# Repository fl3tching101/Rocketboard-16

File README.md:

# Rocketboard-16
 16 key RGB backlit macro board/numpad with two EC11 rotary encoder switches and a 128x64 OLED display

In addition to running [QMK](https://qmk.fm/) the Rocketboard 16 is compatible with [VIA](https://caniusevia.com/) for quick and easy configuration.

The firmware is open source and integrated with the QMK project, it can be found [here](https://github.com/qmk/qmk_firmware/tree/master/keyboards/rocketboard_16).

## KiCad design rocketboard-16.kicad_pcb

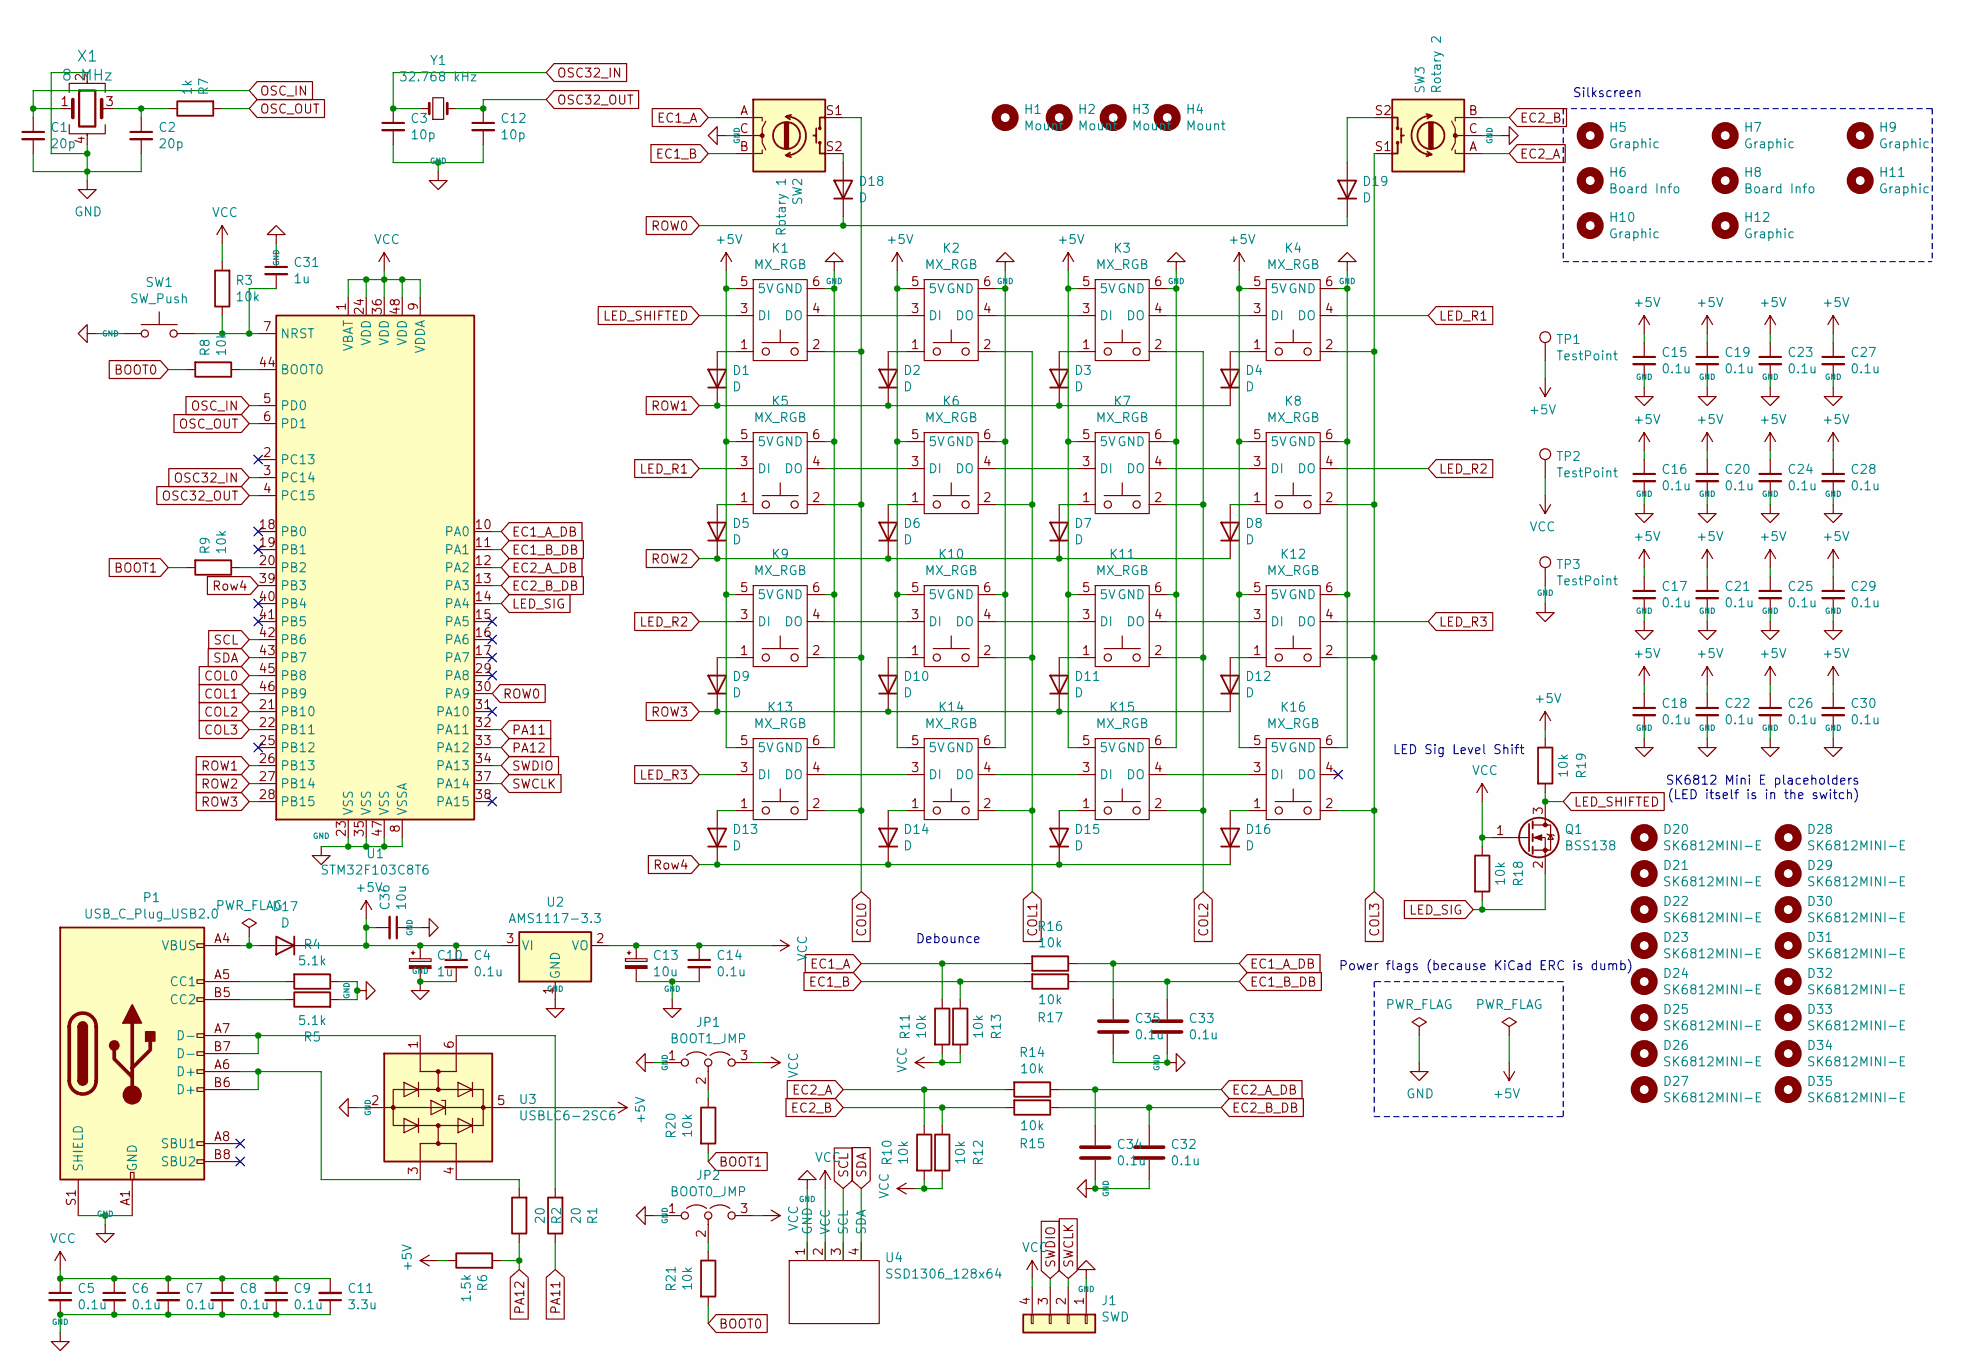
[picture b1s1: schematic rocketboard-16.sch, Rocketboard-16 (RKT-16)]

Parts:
C1, C2: 20p; C_0603_1608Metric
C3, C12: 10p; C_0603_1608Metric
C4, C5, C6, C7, C8, C9, C14, C15, C16, C17, C18, C19, C20, C21, C22, C23, C24, C25, C26, C27, C28, C29, C30, C32, C33, C34, C35: 0.1u; C_0603_1608Metric
C10: 1u; CP_EIA-3216-10_Kemet-I
C11: 3.3u; C_0603_1608Metric
C13: 10u; CP_EIA-3216-10_Kemet-I
C31: 1u; C_0603_1608Metric
C36: 10u; C_0603_1608Metric
D1, D2, D3, D4, D5, D6, D7, D8, D9, D10, D11, D12, D13, D14, D15, D16, D17, D18, D19: D; D_SOD-123
D20, D21, D22, D23, D24, D25, D26, D27, D28, D29, D30, D31, D32, D33, D34, D35: SK6812MINI-E; DUMMY_SK6812MINI-E
H1, H2, H3, H4: Mount; MountingHole_3.2mm_M3
H5: Graphic; saturn_v_simplified
H6: Board Info; board-title
H7: Graphic; lunar_module
H8: Board Info; text
H9: Graphic; space_shuttle
H10: Graphic; iss
H11: Graphic; spacewalk
H12: Graphic; hubble_space_telescope
J1: SWD; PinHeader_1x04_P2.54mm_Vertical
JP1: BOOT1_JMP; SolderJumper-3_P1.3mm_Open_Pad1.0x1.5mm
JP2: BOOT0_JMP; SolderJumper-3_P1.3mm_Open_Pad1.0x1.5mm
K1, K2, K3, K4, K5, K6, K7, K8, K9, K10, K11, K12, K13, K14, K15, K16: MX_RGB; MX_KEYSWITCH_RGB_2D
P1: USB_C_Plug_USB2.0; USB_C_Receptacle_Palconn_UTC16-G
Q1: BSS138; SOT-23
R1, R2: 20; R_0603_1608Metric
R3, R8, R9, R10, R11, R12, R13, R14, R15, R16, R17, R18, R19, R20, R21: 10k; R_0603_1608Metric
R4, R5: 5.1k; R_0603_1608Metric
R6: 1.5k; R_0603_1608Metric
R7: 1k; R_0603_1608Metric
SW1: SW_Push; SW_TS-1187A-B-A-B
SW2: Rotary 1; RotaryEncoder_Alps_EC11E-Switch_Vertical_H20mm_CircularMoun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
SW3: Rotary 2; RotaryEncoder_Alps_EC11E-Switch_Vertical_H20mm_CircularMoun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
TP1, TP2, TP3: TestPoint; TestPoint_Pad_D1.0mm
U1: STM32F103C8T6; LQFP-48_7x7mm_P0.5mm
U2: AMS1117-3.3; SOT-223-3_TabPin2
U3: USBLC6-2SC6; SOT-23-6
U4: SSD1306_128x64; PinHeader_1x04_P2.54mm_Vertical
X1: 8 MHz; Crystal_SMD_5032-4Pin_5.0x3.2mm; Part_num X50328MSB4SI
Y1: 32.768 kHz; Crystal_SMD_3215-2Pin_3.2x1.5mm

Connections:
+5V: C4.1, C10.1, C15.1, C16.1, C17.1, C18.1, C19.1, C20.1, C21.1, C22.1, C23.1, C24.1, C25.1, C26.1, C27.1, C28.1, C29.1, C30.1, C36.2, D17.1 (K), K1.5 (5V), K2.5 (5V), K3.5 (5V), K4.5 (5V), K5.5 (5V), K6.5 (5V), K7.5 (5V), K8.5 (5V), K9.5 (5V), K10.5 (5V), K11.5 (5V), K12.5 (5V), K13.5 (5V), K14.5 (5V), K15.5 (5V), K16.5 (5V), R6.1, R19.1, TP1.1, U2.3 (VI), U3.5 (VBUS)
BOOT0: R8.2, R21.2
BOOT1: R9.2, R20.2
COL0: K1.2, K5.2, K9.2, K13.2, SW2.S1, U1.45 (PB8)
COL1: K2.2, K6.2, K10.2, K14.2, U1.46 (PB9)
COL2: K3.2, K7.2, K11.2, K15.2, U1.21 (PB10)
COL3: K4.2, K8.2, K12.2, K16.2, SW3.S1, U1.22 (PB11)
EC1_A: R11.1, R16.2, SW2.A
EC1_A_DB: C35.1, R16.1, U1.10 (PA0)
EC1_B: R13.1, R17.2, SW2.B
EC1_B_DB: C33.1, R17.1, U1.11 (PA1)
EC2_A: R10.1, R14.2, SW3.A
EC2_A_DB: C34.1, R14.1, U1.12 (PA2)
EC2_B: R12.1, R15.2, SW3.B
EC2_B_DB: C32.1, R15.1, U1.13 (PA3)
GND: C1.2, C2.2, C3.2, C4.2, C5.2, C6.2, C7.2, C8.2, C9.2, C10.2, C11.1, C12.2, C13.2, C14.2, C15.2, C16.2, C17.2, C18.2, C19.2, C20.2, C21.2, C22.2, C23.2, C24.2, C25.2, C26.2, C27.2, C28.2, C29.2, C30.2, C31.1, C32.2, C33.2, C34.2, C35.2, C36.1, J1.1, JP1.1 (A), JP2.1 (A), K1.6 (GND), K2.6 (GND), K3.6 (GND), K4.6 (GND), K5.6 (GND), K6.6 (GND), K7.6 (GND), K8.6 (GND), K9.6 (GND), K10.6 (GND), K11.6 (GND), K12.6 (GND), K13.6 (GND), K14.6 (GND), K15.6 (GND), K16.6 (GND), P1.A1 (GND), P1.A12 (GND), P1.B1 (GND), P1.B12 (GND), P1.S1 (SHIELD), R4.1, R5.2, SW1.1, SW2.C, SW3.C, TP3.1, U1.8 (VSSA), U1.23 (VSS), U1.35 (VSS), U1.47 (VSS), U2.1 (GND), U3.2 (GND), U4.1 (GND), X1.2, X1.4
LED_R1: K4.4 (DO), K5.3 (DI)
LED_R2: K8.4 (DO), K9.3 (DI)
LED_R3: K12.4 (DO), K13.3 (DI)
LED_SHIFTED: K1.3 (DI), Q1.3 (D), R19.2
LED_SIG: Q1.2 (S), R18.2, U1.14 (PA4)
unnamed: C2.1, R7.1, X1.3
unnamed: C31.2, R3.1, SW1.2, U1.7 (NRST)
unnamed: D1.2 (A), K1.1
unnamed: D2.2 (A), K2.1
unnamed: D3.2 (A), K3.1
unnamed: D4.2 (A), K4.1
unnamed: D5.2 (A), K5.1
unnamed: D6.2 (A), K6.1
unnamed: D7.2 (A), K7.1
unnamed: D8.2 (A), K8.1
unnamed: D9.2 (A), K9.1
unnamed: D10.2 (A), K10.1
unnamed: D11.2 (A), K11.1
unnamed: D12.2 (A), K12.1
unnamed: D13.2 (A), K13.1
unnamed: D14.2 (A), K14.1
unnamed: D15.2 (A), K15.1
unnamed: D16.2 (A), K16.1
unnamed: D17.2 (A), P1.A4 (VBUS), P1.A9 (VBUS), P1.B4 (VBUS), P1.B9 (VBUS)
unnamed: D18.2 (A), SW2.S2
unnamed: D19.2 (A), SW3.S2
unnamed: JP1.2 (C), R20.1
unnamed: JP2.2 (C), R21.1
unnamed: K1.4 (DO), K2.3 (DI)
unnamed: K2.4 (DO), K3.3 (DI)
unnamed: K3.4 (DO), K4.3 (DI)
unnamed: K5.4 (DO), K6.3 (DI)
unnamed: K6.4 (DO), K7.3 (DI)
unnamed: K7.4 (DO), K8.3 (DI)
unnamed: K9.4 (DO), K10.3 (DI)
unnamed: K10.4 (DO), K11.3 (DI)
unnamed: K11.4 (DO), K12.3 (DI)
unnamed: K13.4 (DO), K14.3 (DI)
unnamed: K14.4 (DO), K15.3 (DI)
unnamed: K15.4 (DO), K16.3 (DI)
unnamed: P1.A5 (CC1), R4.2
unnamed: P1.A6 (D+), P1.B6 (D+), U3.3 (I/O2)
unnamed: P1.A7 (D-), P1.B7 (D-), U3.1 (I/O1)
unnamed: P1.B5 (CC2), R5.1
unnamed: R1.2, U3.6 (I/O1)
unnamed: R2.2, U3.4 (I/O2)
unnamed: R8.1, U1.44 (BOOT0)
unnamed: R9.1, U1.20 (PB2)
OSC32_IN: C3.1, U1.3 (PC14), Y1.1
OSC32_OUT: C12.1, U1.4 (PC15), Y1.2
OSC_IN: C1.1, U1.5 (PD0), X1.1
OSC_OUT: R7.2, U1.6 (PD1)
PA11: R1.1, U1.32 (PA11)
PA12: R2.1, R6.2, U1.33 (PA12)
ROW0: D18.1 (K), D19.1 (K), U1.30 (PA9)
ROW1: D1.1 (K), D2.1 (K), D3.1 (K), D4.1 (K), U1.26 (PB13)
ROW2: D5.1 (K), D6.1 (K), D7.1 (K), D8.1 (K), U1.27 (PB14)
ROW3: D9.1 (K), D10.1 (K), D11.1 (K), D12.1 (K), U1.28 (PB15)
Row4: D13.1 (K), D14.1 (K), D15.1 (K), D16.1 (K), U1.39 (PB3)
SCL: U1.42 (PB6), U4.3 (SCL)
SDA: U1.43 (PB7), U4.4 (SDA)
SWCLK: J1.2, U1.37 (PA14)
SWDIO: J1.3, U1.34 (PA13)
VCC: C5.1, C6.1, C7.1, C8.1, C9.1, C11.2, C13.1, C14.1, J1.4, JP1.3 (B), JP2.3 (B), Q1.1 (G), R3.2, R10.2, R11.2, R12.2, R13.2, R18.1, TP2.1, U1.1 (VBAT), U1.9 (VDDA), U1.24 (VDD), U1.36 (VDD), U1.48 (VDD), U2.2 (VO), U4.2 (VCC)

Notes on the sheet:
SK6812 Mini E placeholders (LED itself is in the switch)
Power flags (because KiCad ERC is dumb)
Silkscreen
Debounce
LED Sig Level Shift

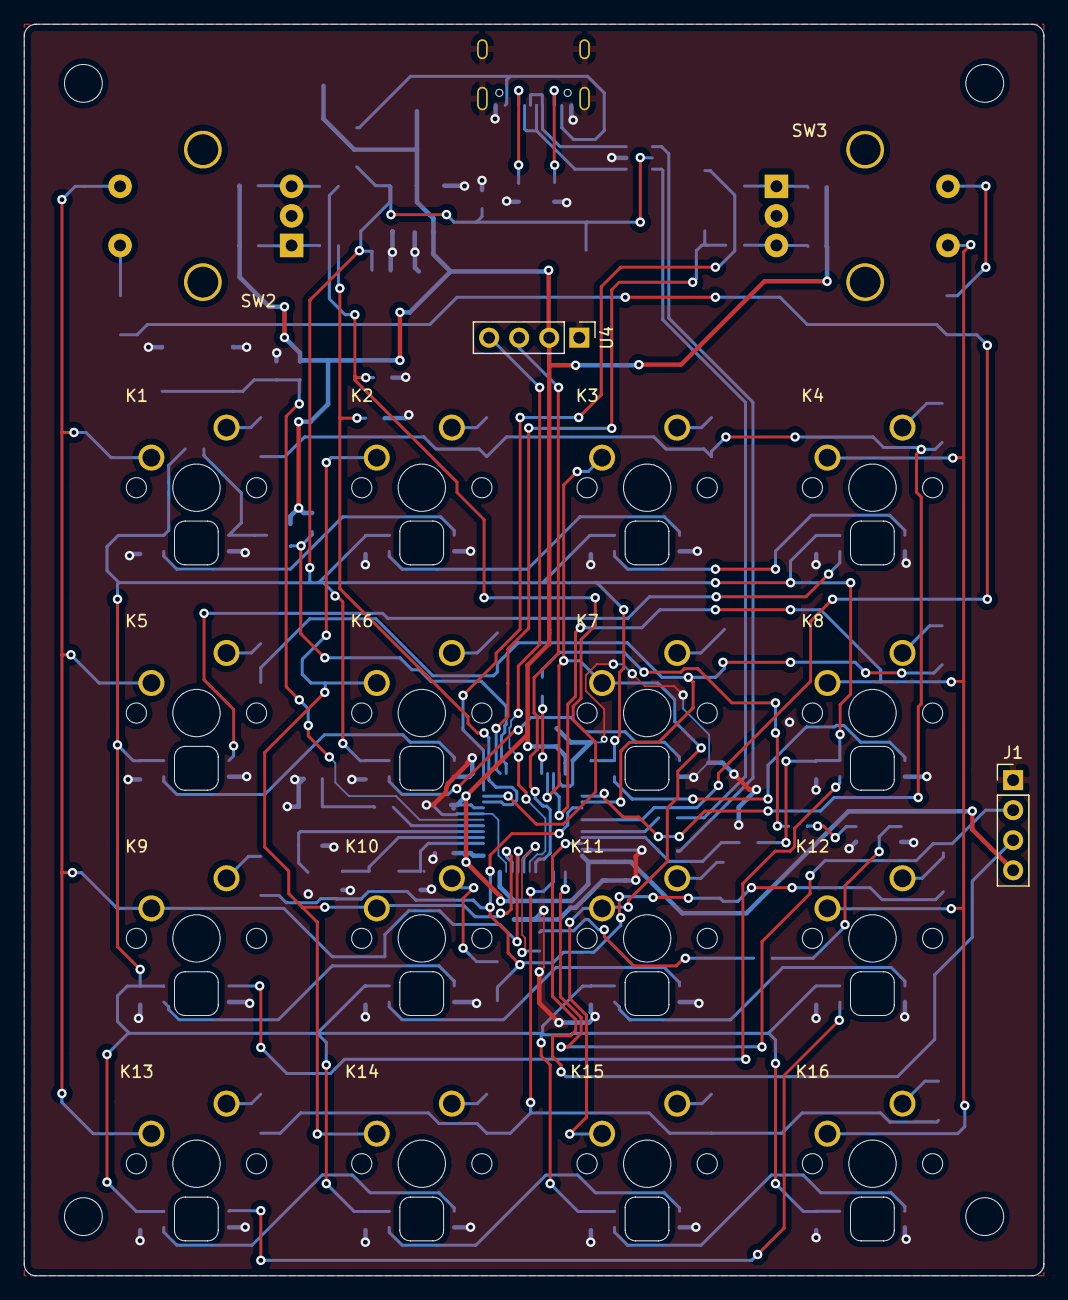
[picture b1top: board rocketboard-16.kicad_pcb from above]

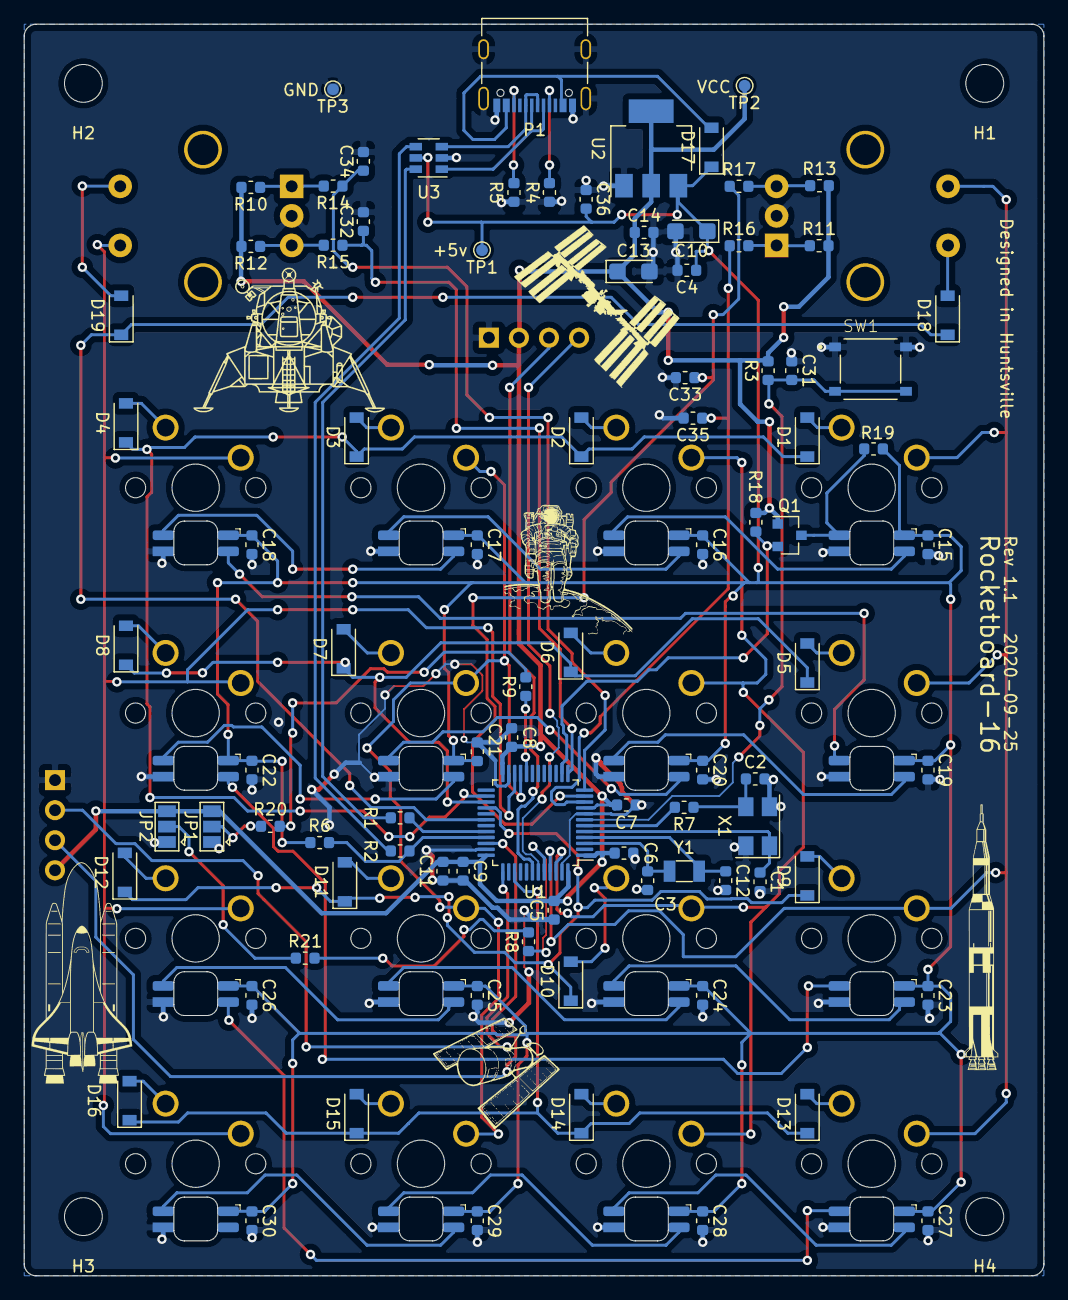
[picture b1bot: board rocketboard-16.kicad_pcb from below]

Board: 2 copper layers, 86.2 x 105.8 mm, 137 parts (117 on the bottom side), 80 nets.

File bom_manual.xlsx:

Qty | Reference(s) | Value | Footprint | MPN | Vender | Vender Part # | Manufacturer | DNP | Cost | Board Cost | Notes
2 | C1, C2 | 20p | Capacitor_SMD:C_0603_1608Metric | CL10C200JB8NNNC | JLCPCB | C1648 | Samsung Electro-Mechanics |  | 8.5000000000000006E-3 | 1.7000000000000001E-2
2 | C3, C12 | 10p | Capacitor_SMD:C_0603_1608Metric | CL10C100JB8NNNC | JLCPCB | C1634 | Samsung Electro-Mechanics |  | 8.3000000000000001E-3 | 1.66E-2 | Only to be loaded on prototypes unless a use is found for the LSE (RTC) oscilla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
27 | C4, C5, C6, C7, C8, C9, C14, C15, C16, C17, C18, C19, C20, C21, C22, C23, C24, 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 | 0.1u | Capacitor_SMD:C_0603_1608Metric | CC0603KRX7R9BB104 | JLCPCB | C14663 | YAGEO |  | 6.7999999999999996E-3 | 0.18359999999999999
1 | C10 | 1u | Capacitor_Tantalum_SMD:CP_EIA-3216-10_Kemet-I | CA45-A-16V-1uF-K | JLCPCB | C140386 | Shenzhen Zhenhua XinYun Elec |  | 7.1599999999999997E-2 | 7.1599999999999997E-2 | POLARIZED!!!
1 | C11 | 3.3u | Capacitor_SMD:C_0603_1608Metric | CL10A335KP8NNNC | JLCPCB | C51412 | Samsung Electro-Mechanics |  | 1.7000000000000001E-2 | 1.7000000000000001E-2 | Only 10v, careful!
1 | C13 | 10u | Capacitor_Tantalum_SMD:CP_EIA-3216-10_Kemet-I | TAJA106K016RNJ | JLCPCB | C7171 | AVX |  | 0.15490000000000001 | 0.15490000000000001
1 | C31 | 1u | Capacitor_SMD:C_0603_1608Metric | CL10A105KB8NNNC | JLCPCB | C15849 | Samsung Electro-Mechanics |  | 1.29E-2 | 1.29E-2
1 | C36 | 10u | Capacitor_SMD:C_0603_1608Metric | CL10A106MA8NRNC | LCSC | C96446 | Samsung Electro-Mechanics | Yes | 3.3354000000000002E-2 | 3.3354000000000002E-2
19 | D1, D2, D3, D4, D5, D6, D7, D8, D9, D10, D11, D12, D13, D14, D15, D16, D17, D18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 | D | Diode_SMD:D_SOD-123 | 1N4148W | JLCPCB | C81598 | Semtech |  | 1.4E-2 | 0.26600000000000001
16 | D20, D21, D22, D23, D24, D25, D26, D27, D28, D29, D30, D31, D32, D33, D34, D35 | SK6812MINI-E | seth-keyboard:DUMMY_SK6812MINI-E | YS-SK6812MINI-E | AliExpress |  | Yushakobo | Yes | 0.10489999999999999 | 1.6783999999999999 | Cannot find anywhere but AliExpress, will have to be hand soldered for the time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
4 | H1, H2, H3, H4 | Mount | MountingHole:MountingHole_3.2mm_M3 |  |  |  |  | Yes |  | 0 | Nothing to be loaded
1 | H5 | Graphic | seth-logo:saturn_v_simplified |  |  |  |  |  |  | 0
1 | H6 | Board Info | seth-logo:board-title |  |  |  |  |  |  | 0
1 | H7 | Graphic | seth-logo:lunar_module |  |  |  |  |  |  | 0
1 | H8 | Board Info | seth-logo:text |  |  |  |  |  |  | 0
1 | H9 | Graphic | seth-logo:space_shuttle |  |  |  |  |  |  | 0
1 | H10 | Graphic | seth-logo:iss |  |  |  |  |  |  | 0
1 | H11 | Graphic | seth-logo:spacewalk |  |  |  |  |  |  | 0
1 | H12 | Graphic | seth-logo:hubble_space_telescope |  |  |  |  |  |  | 0
1 | J1 | SWD | Connector_PinHeader_2.54mm:PinHeader_1x04_P2.54mm_Vertical |  |  |  |  | Yes |  | 0 | Will only be loaded for debugging purposes
1 | JP1 | BOOT1_JMP | Jumper:SolderJumper-3_P1.3mm_Open_Pad1.0x1.5mm |  |  |  |  | Yes |  | 0 | Is only a footprint
1 | JP2 | BOOT0_JMP | Jumper:SolderJumper-3_P1.3mm_Open_Pad1.0x1.5mm |  |  |  |  | Yes |  | 0 | Is only a footprint
16 | K1, K2, K3, K4, K5, K6, K7, K8, K9, K10, K11, K12, K13, K14, K15, K16 | MX_RGB | seth-keyboard:MX_KEYSWITCH_RGB_2D |  |  |  |  | Yes |  | 0 | Footprint only, user will load own switch
1 | P1 | USB_C_Plug_USB2.0 | Connector_USB:USB_C_Receptacle_Palconn_UTC16-G | MC-311D | LCSC | C136423 | SOFNG | Yes | 0.84499999999999997 | 0.84499999999999997 | Not carried by JLCPCB - mounting pins may not be long enough for 1.6mm board!
1 | Q1 | BSS138 | Package_TO_SOT_SMD:SOT-23 | BSS138 | LCSC | C489349 | KEXIN |  | 1.7343000000000001E-2 | 1.7343000000000001E-2
2 | R1, R2 | 20 | Resistor_SMD:R_0603_1608Metric | 0603WAF200JT5E | JLCPCB | C22950 | Uniroyal Elec |  | 1.6000000000000001E-3 | 3.2000000000000002E-3
15 | R3, R8, R9, R10, R11, R12, R13, R14, R15, R16, R17, R18, R19, R20, R21 | 10k | Resistor_SMD:R_0603_1608Metric | 0603WAF1002T5E | JLCPCB | C25804 | Uniroyal Elec |  | 2E-3 | 0.03
2 | R4, R5 | 5.1k | Resistor_SMD:R_0603_1608Metric | 0603WAF5101T5E | JLCPCB | C23186 | Uniroyal Elec |  | 1.9E-3 | 3.8E-3
1 | R6 | 1.5k | Resistor_SMD:R_0603_1608Metric | 0603WAF1501T5E | JLCPCB | C22843 | Uniroyal Elec |  | 1.8E-3 | 1.8E-3
1 | R7 | 1k | Resistor_SMD:R_0603_1608Metric | 0603WAF1001T5E | JLCPCB | C21190 | Uniroyal Elec |  | 2.0999999999999999E-3 | 2.0999999999999999E-3
1 | SW1 | SW_Push | Button_Switch_SMD:SW_Push_1P1T_NO_6x6mm_H9.5mm | TS-1187A-C-C-B | JLCPCB | C318889 | XKB Enterprise |  | 3.4799999999999998E-2 | 3.4799999999999998E-2
1 | SW2 | Rotary 1 | seth-buttons:RotaryEncoder_Alps_EC11E-Switch_Vertical_H20mm_CircularMountingHol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 | EC11E1534408 | LCSC | C278348 | ALPS Electric | Yes | 1.943333 | 1.943333
1 | SW3 | Rotary 2 | seth-buttons:RotaryEncoder_Alps_EC11E-Switch_Vertical_H20mm_CircularMountingHol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 | EC11E1534408 | LCSC | C278348 | ALPS Electric | Yes | 1.943333 | 1.943333
1 | U1 | STM32F103C8T6 | Package_QFP:LQFP-48_7x7mm_P0.5mm | STM32F103C8T6 | JLCPCB | C8734 | STMicroelectronics |  | 1.4413 | 1.4413
1 | U2 | AMS1117-3.3 | Package_TO_SOT_SMD:SOT-223-3_TabPin2 | AMS1117-3.3 | JLCPCB | C6186 | Advanced Monolithic Systems |  | 0.124 | 0.124
1 | U3 | USBLC6-2SC6 | Package_TO_SOT_SMD:SOT-23-6 | USBLC6-2SC6 | JLCPCB | C7519 | STMicroelectronics |  | 9.1499999999999998E-2 | 9.1499999999999998E-2
1 | U4 | SSD1306_128x64 | Connector_PinHeader_2.54mm:PinHeader_1x04_P2.54mm_Vertical | MTF185-104SY1 | LCSC | C358718 | MINTRON | Yes | 5.4961000000000003E-2 | 5.4961000000000003E-2
1 | X1 | 8 MHz | Crystal:Crystal_SMD_5032-4Pin_5.0x3.2mm | X50328MSB4SI | JLCPCB | C157341 | Yangxing Tech |  | 0.21870000000000001 | 0.21870000000000001
1 | Y1 | 32.768 kHz | Crystal:Crystal_SMD_3215-2Pin_3.2x1.5mm | Q13FC1350000200 | JLCPCB | C48615 | Seiko Epson |  | 0.2336 | 0.2336 | Only to be loaded on prototypes unless a use is found for the LSE (RTC) oscilla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
 |  |  |  |  |  |  | Unique parts (loaded) count: |  |  | JLCPCB Cost:
 |  |  |  |  |  |  | 28 |  |  | 2.9417430000000002
 |  |  |  |  |  |  | Number of loaded SMD parts: |  |  | Other Cost:
 |  |  |  |  |  |  | 90 |  |  | 6.4983809999999993
 |  |  |  |  |  |  | Number of parts: |  |  | Total Cost:
 |  |  |  |  |  |  | 134 |  |  | 9.4401239999999991
 | Alternates:
1 | U2 | AMS1117-3.3 | Package_TO_SOT_SMD:SOT-223-3_TabPin2 | AMS1117-3.3 | JLCPCB | C347222 | UMW(Youtai Semiconductor Co., Ltd.) |  | 0.124 | 0.124
1 | Y1 | 32.768 kHz | Crystal:Crystal_SMD_3215-2Pin_3.2x1.5mm | X1A000141000100 | JLCPCB | C94674 | Seiko Epson |  | 0.2336 | 0.2336 | Only to be loaded on prototypes unless a use is found for the LSE (RTC) oscilla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
27 | C4, C5, C6, C7, C8, C9, C14, C15, C16, C17, C18, C19, C20, C21, C22, C23, C24, 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 | 0.1u | Capacitor_SMD:C_0603_1608Metric | FN18F104Z500PSG | JLCPCB | C497032 | PSA(Prosperity Dielectrics) |  | 3.0119999999999999E-3 | 8.1323999999999994E-2

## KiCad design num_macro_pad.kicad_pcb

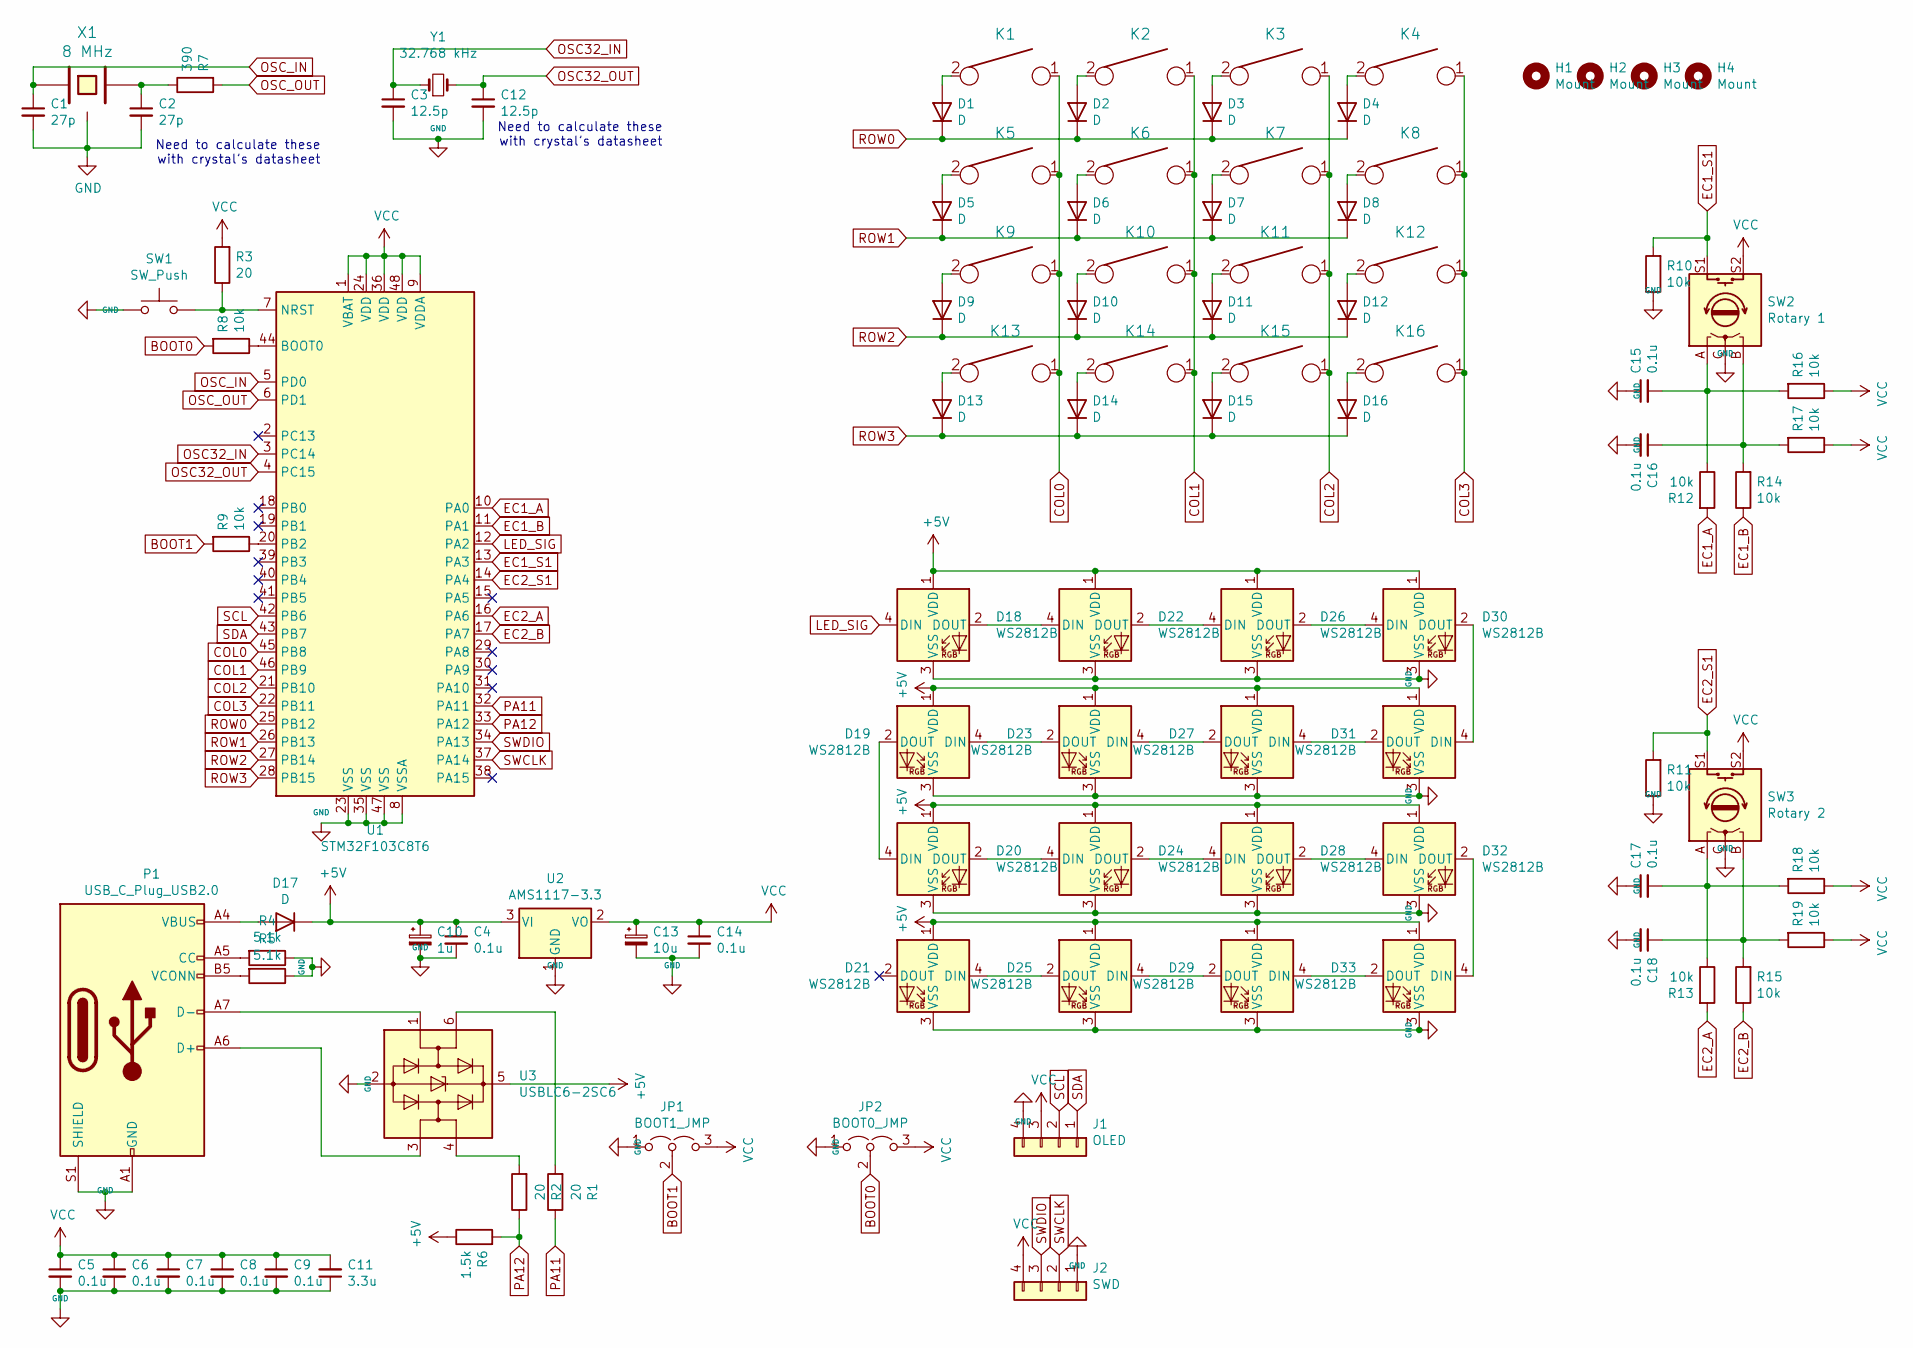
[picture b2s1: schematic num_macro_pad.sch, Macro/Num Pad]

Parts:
C1, C2: 27p; C_0603_1608Metric
C3, C12: 12.5p; C_0603_1608Metric
C4, C5, C6, C7, C8, C9, C14, C15, C16, C17, C18: 0.1u; C_0603_1608Metric
C10: 1u; C_0603_1608Metric
C11: 3.3u; C_0603_1608Metric
C13: 10u; C_0603_1608Metric
D1, D2, D3, D4, D5, D6, D7, D8, D9, D10, D11, D12, D13, D14, D15, D16, D17: D; D_0603_1608Metric
D18, D19, D20, D21, D22, D23, D24, D25, D26, D27, D28, D29, D30, D31, D32, D33: WS2812B; LED_WS2812B_PLCC4_5.0x5.0mm_P3.2mm
H1, H2, H3, H4: Mount; MountingHole_3.2mm_M3
J1: OLED; PinHeader_1x04_P2.54mm_Vertical
J2: SWD; PinHeader_1x04_P2.54mm_Vertical
JP1: BOOT1_JMP; SolderJumper-3_P1.3mm_Open_Pad1.0x1.5mm
JP2: BOOT0_JMP; SolderJumper-3_P1.3mm_Open_Pad1.0x1.5mm
K1, K2, K3, K4, K5, K6, K7, K8, K9, K10, K11, K12, K13, K14, K15, K16: KEYSW; SW_Cherry_MX_1.00u_PCB
P1: USB_C_Plug_USB2.0; USB_C_Receptacle_HRO_TYPE-C-31-M-12
R1, R2, R3: 20; R_0603_1608Metric
R4, R5: 5.1k; R_0603_1608Metric
R6: 1.5k; R_0603_1608Metric
R7: 390; R_0603_1608Metric
R8, R9, R10, R11, R12, R13, R14, R15, R16, R17, R18, R19: 10k; R_0603_1608Metric
SW1: SW_Push; SW_Push_1P1T_NO_6x6mm_H9.5mm
SW2: Rotary 1; RotaryEncoder_Alps_EC11E-Switch_Vertical_H20mm
SW3: Rotary 2; RotaryEncoder_Alps_EC11E-Switch_Vertical_H20mm
U1: STM32F103C8T6; LQFP-48_7x7mm_P0.5mm
U2: AMS1117-3.3; SOT-223-3_TabPin2
U3: USBLC6-2SC6; SOT-23-6
X1: 8 MHz; Crystal_SMD_5032-4Pin_5.0x3.2mm
Y1: 32.768 kHz; Crystal_SMD_3215-2Pin_3.2x1.5mm

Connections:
+5V: C4.1, C10.1, D17.1 (K), D18.1 (VDD), D19.1 (VDD), D20.1 (VDD), D21.1 (VDD), D22.1 (VDD), D23.1 (VDD), D24.1 (VDD), D25.1 (VDD), D26.1 (VDD), D27.1 (VDD), D28.1 (VDD), D29.1 (VDD), D30.1 (VDD), D31.1 (VDD), D32.1 (VDD), D33.1 (VDD), R6.1, U2.3 (VI), U3.5 (VBUS)
BOOT0: JP2.2 (C), R8.2
BOOT1: JP1.2 (C), R9.2
COL0: K1.1, K5.1, K9.1, K13.1, U1.45 (PB8)
COL1: K2.1, K6.1, K10.1, K14.1, U1.46 (PB9)
COL2: K3.1, K7.1, K11.1, K15.1, U1.21 (PB10)
COL3: K4.1, K8.1, K12.1, K16.1, U1.22 (PB11)
EC1_A: R12.2, U1.10 (PA0)
EC1_B: R14.1, U1.11 (PA1)
EC1_S1: R10.2, SW2.S1, U1.13 (PA3)
EC2_A: R13.2, U1.16 (PA6)
EC2_B: R15.1, U1.17 (PA7)
EC2_S1: R11.2, SW3.S1, U1.14 (PA4)
LED_SIG: D18.4 (DIN), U1.12 (PA2)
unnamed: C15.2, R12.1, R16.2, SW2.A
unnamed: C16.1, R14.2, R17.2, SW2.B
unnamed: C17.2, R13.1, R18.2, SW3.A
unnamed: C18.1, R15.2, R19.2, SW3.B
unnamed: D1.2 (A), K1.2
unnamed: D2.2 (A), K2.2
unnamed: D3.2 (A), K3.2
unnamed: D4.2 (A), K4.2
unnamed: D5.2 (A), K5.2
unnamed: D6.2 (A), K6.2
unnamed: D7.2 (A), K7.2
unnamed: D8.2 (A), K8.2
unnamed: D9.2 (A), K9.2
unnamed: D10.2 (A), K10.2
unnamed: D11.2 (A), K11.2
unnamed: D12.2 (A), K12.2
unnamed: D13.2 (A), K13.2
unnamed: D14.2 (A), K14.2
unnamed: D15.2 (A), K15.2
unnamed: D16.2 (A), K16.2
unnamed: D17.2 (A), P1.A4 (VBUS), P1.A9 (VBUS), P1.B4 (VBUS), P1.B9 (VBUS)
unnamed: D18.2 (DOUT), D22.4 (DIN)
unnamed: D19.2 (DOUT), D20.4 (DIN)
unnamed: D19.4 (DIN), D23.2 (DOUT)
unnamed: D20.2 (DOUT), D24.4 (DIN)
unnamed: D21.4 (DIN), D25.2 (DOUT)
unnamed: D22.2 (DOUT), D26.4 (DIN)
unnamed: D23.4 (DIN), D27.2 (DOUT)
unnamed: D24.2 (DOUT), D28.4 (DIN)
unnamed: D25.4 (DIN), D29.2 (DOUT)
unnamed: D26.2 (DOUT), D30.4 (DIN)
unnamed: D27.4 (DIN), D31.2 (DOUT)
unnamed: D28.2 (DOUT), D32.4 (DIN)
unnamed: D29.4 (DIN), D33.2 (DOUT)
unnamed: D30.2 (DOUT), D31.4 (DIN)
unnamed: D32.2 (DOUT), D33.4 (DIN)
unnamed: P1.A5 (CC), R4.2
unnamed: P1.A6 (D+), U3.3 (I/O2)
unnamed: P1.A7 (D-), U3.1 (I/O1)
unnamed: P1.B5 (VCONN), R5.2
unnamed: R1.2, U3.6 (I/O1)
unnamed: R2.2, U3.4 (I/O2)
unnamed: R3.1, SW1.2, U1.7 (NRST)
unnamed: R8.1, U1.44 (BOOT0)
unnamed: R9.1, U1.20 (PB2)
OSC32_IN: C3.1, U1.3 (PC14), Y1.1
OSC32_OUT: C12.1, U1.4 (PC15), Y1.2
OSC_IN: C1.1, U1.5 (PD0), X1.1
OSC_OUT: R7.2, U1.6 (PD1)
PA11: R1.1, U1.32 (PA11)
PA12: R2.1, R6.2, U1.33 (PA12)
ROW0: D1.1 (K), D2.1 (K), D3.1 (K), D4.1 (K), U1.25 (PB12)
ROW1: D5.1 (K), D6.1 (K), D7.1 (K), D8.1 (K), U1.26 (PB13)
ROW2: D9.1 (K), D10.1 (K), D11.1 (K), D12.1 (K), U1.27 (PB14)
ROW3: D13.1 (K), D14.1 (K), D15.1 (K), D16.1 (K), U1.28 (PB15)
SCL: J1.2, U1.42 (PB6)
SDA: J1.1, U1.43 (PB7)
SWCLK: J2.2, U1.37 (PA14)
SWDIO: J2.3, U1.34 (PA13)
VCC: C5.1, C6.1, C7.1, C8.1, C9.1, C11.2, C13.1, C14.1, J1.3, J2.4, JP1.3 (B), JP2.3 (B), R3.2, R16.1, R17.1, R18.1, R19.1, SW2.S2, SW3.S2, U1.1 (VBAT), U1.9 (VDDA), U1.24 (VDD), U1.36 (VDD), U1.48 (VDD), U2.2 (VO)

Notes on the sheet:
Need to calculate these with crystal's datasheet

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
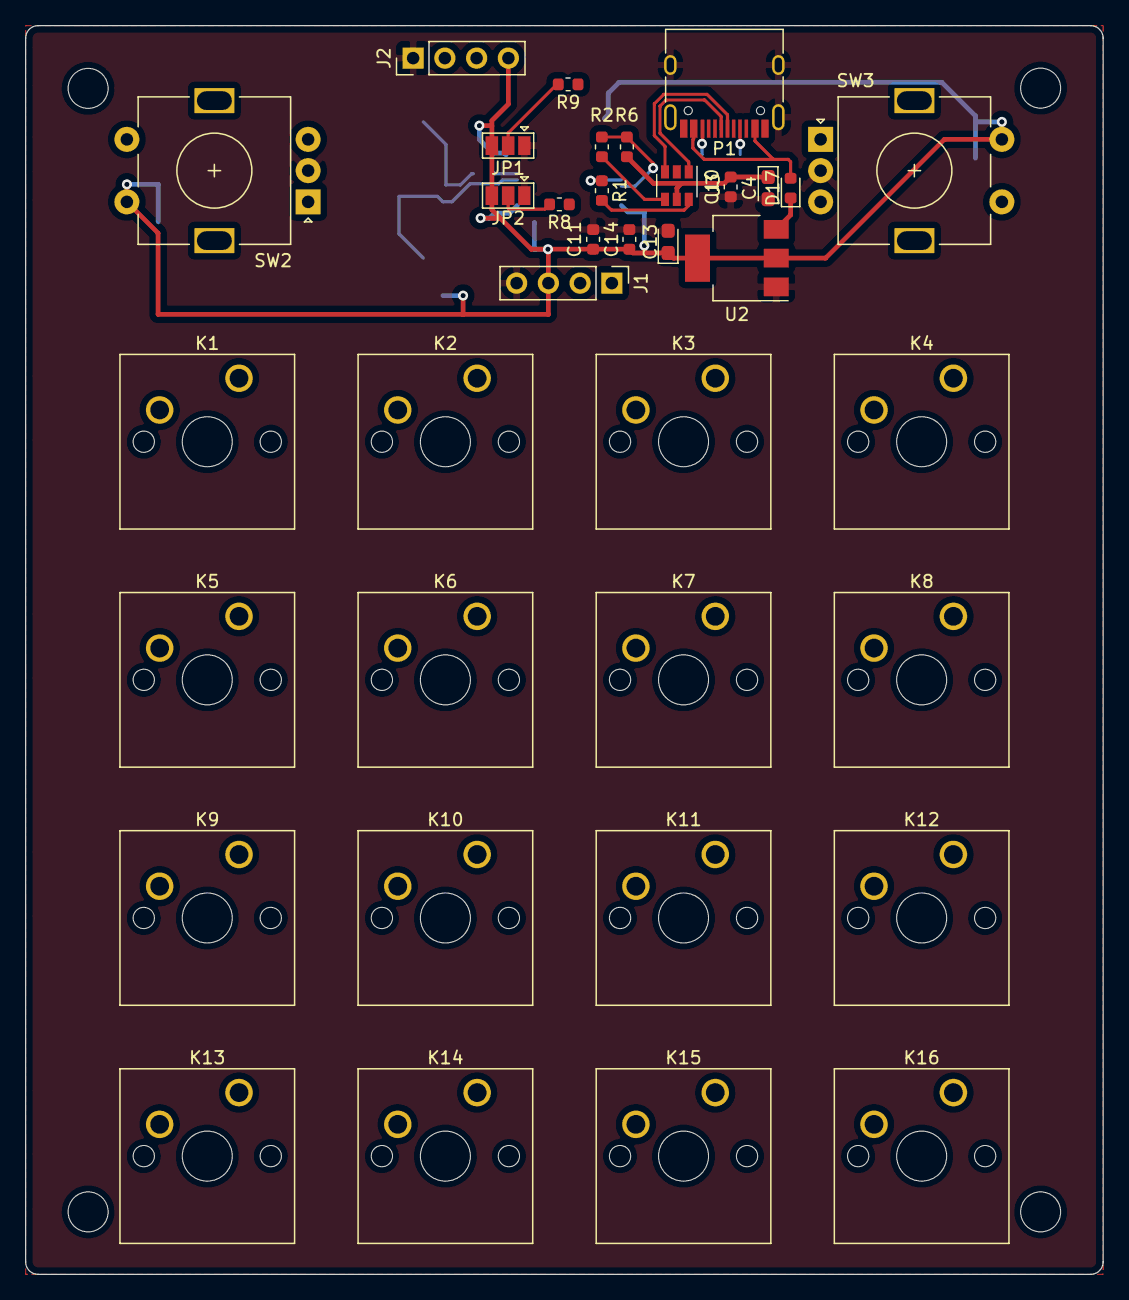
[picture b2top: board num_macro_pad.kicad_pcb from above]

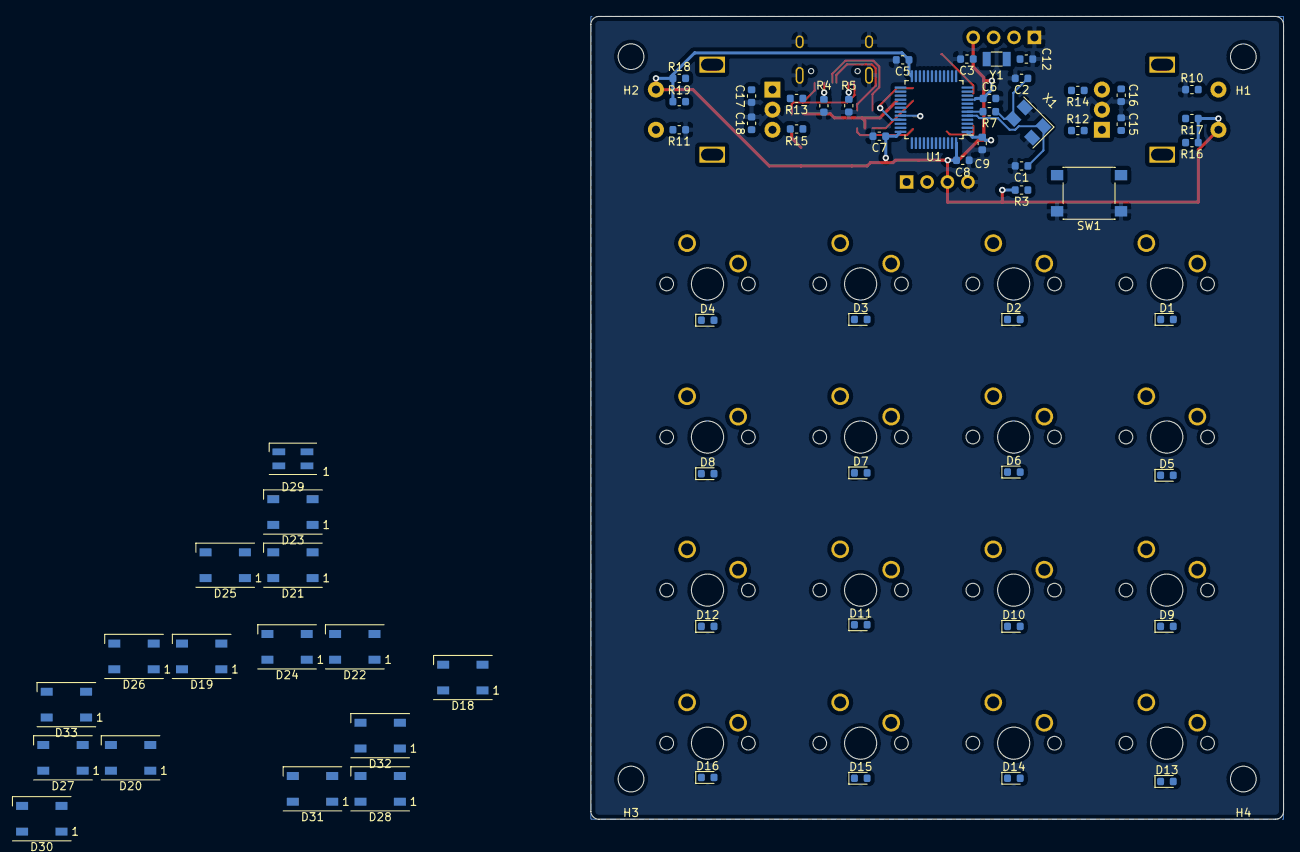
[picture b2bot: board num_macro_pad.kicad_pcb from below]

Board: 2 copper layers, 86.2 x 99.9 mm, 103 parts (67 on the bottom side), 76 nets.

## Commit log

2020-09-09 Initial commit - bad routing and bad backlighting
    Backup of bad version before I begin fixing
2020-09-09 Fixed the schematic issues (replaced keyswitch symbol for RGB LED, removed old LEDs, replaced USB-C connector), and moved those changes to PCBNew, but have not put all components onto board yet.
2020-09-10 Placed all componenets onto PCB and added josh's 3D model library in to get better 3D previews
2020-09-10 Fixed some of the 3D model references, added a symbol/footprint for the SSD1306 OLED display with a 3D model for pictures, and added draft logo with board info
2020-09-11 Extended PCB height to accomodate the OLED display. Changed the board color to black for previews. Moved components up to take up new space from increasing height of board.
2020-09-11 Routed the two crystals
2020-09-12 Routed most of the wires, many still needed though. Changed a couple of pins around on the schematic due to simpler routing paths.
2020-09-13 Routed more traces. Only lacking a few more connections except for ground. Had to move some pins around to make room, though the change did not help with routing so far.
2020-09-14 Finished all routing, very messy, but theoretically should work
2020-09-14 Generated the gerber files, placed in a folder, and zipped them for uploading. Also had to regenerate the fill.
2020-09-15 Moved the display 3D model to its own folder
2020-09-15 Updated symbols and footprints to use project specific files (portability). Changed one via, was only one smaller than rest.
2020-09-15 Updated schematic and pcb as I found specific parts for BOM, now board needs routing for the diodes on the switches. Created a BOM spreadsheet for manual entry of part numbers, venders, prices, etc.
2020-09-16 Finished adding items to the BOM, added a tactile switch from JLCPCB footprint instead of the one I had
2020-09-16 Connected up all the components that changed due to BOM items. Still has one missing fill connection for some reason.
2020-09-18 Updated the graphics, added some more, and made some slight changed to some components
2020-09-18 Regenerated the gerber files
2020-09-18 Plotted schematic
2020-09-18 Ignored the backup excel file
2020-09-19 Needed to add debounce and pullups to the rotary encoder lines, added to sch and updated PCB
2020-09-19 Updated gerbers
2020-09-23 Added hubble, iss, and spacewalk graphics to sch/pcb
2020-09-23 Updated schematic plot
2020-09-23 Generated gerbers/drill files
2020-09-23 Added JLC text for JLC's part number to the schematic
2020-09-23 Removed JLC text (will pay the $1.50 to not have it on board)
2020-09-23 Added LCSC specific BOM, added the backup shadow excel sheet to gitignore
2020-09-23 Updated the USB-C footprint to match the LCSC USB-C connector that works best (>1mm mounting pins)
2020-09-23 Changed the USB type C connector for one that fits the footprint of the LCSC part - had to adjust clearance on some pins for DRC and re-route some connections
2020-09-23 Regenerated gerbers/drill files
2020-09-23 Re-plotted schematic
2020-09-25 Updated BOMs for alternate part so that it doesn't need backordered from LCSC
2020-09-25 Added in a level shifting circuit for the LED signal (needs 5v sig, not 3.3v), added a 10uf cap on the 5v line for smoothing out possible spikey power draw from LEDs, and added test points on +5v, VC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
2020-09-25 Updated schematic
2020-09-25 Updated BOMs to reflect changes
2020-09-25 Updated BOMs (to fix some duplicate items issues) and added a cost spreadsheet to keep up with the cost of the prototype design
2020-09-25 Updated design to include 10k resistors between boot select jumpers and MCU
2020-09-25 Updated schematic PDF
2020-09-25 Updated all dates and then updated gerbers/pdfs
2020-09-25 Updated boms with another alternate part, 0.1uf resistors were OOS
2020-09-28 Updated prototype costs after ordering most parts, still lacking rotary encoder knobs, and minor updates to PCB that didn't get committed before
2021-12-10 Remove unnecessary folder of symbols/footprints
2021-12-10 Update bom_manual.xlsx
    Old change that never made it to GH
2021-12-10 Added images
2021-12-11 Make README more interesting and helpful
2021-12-11 Clean up image sizes and alignment
